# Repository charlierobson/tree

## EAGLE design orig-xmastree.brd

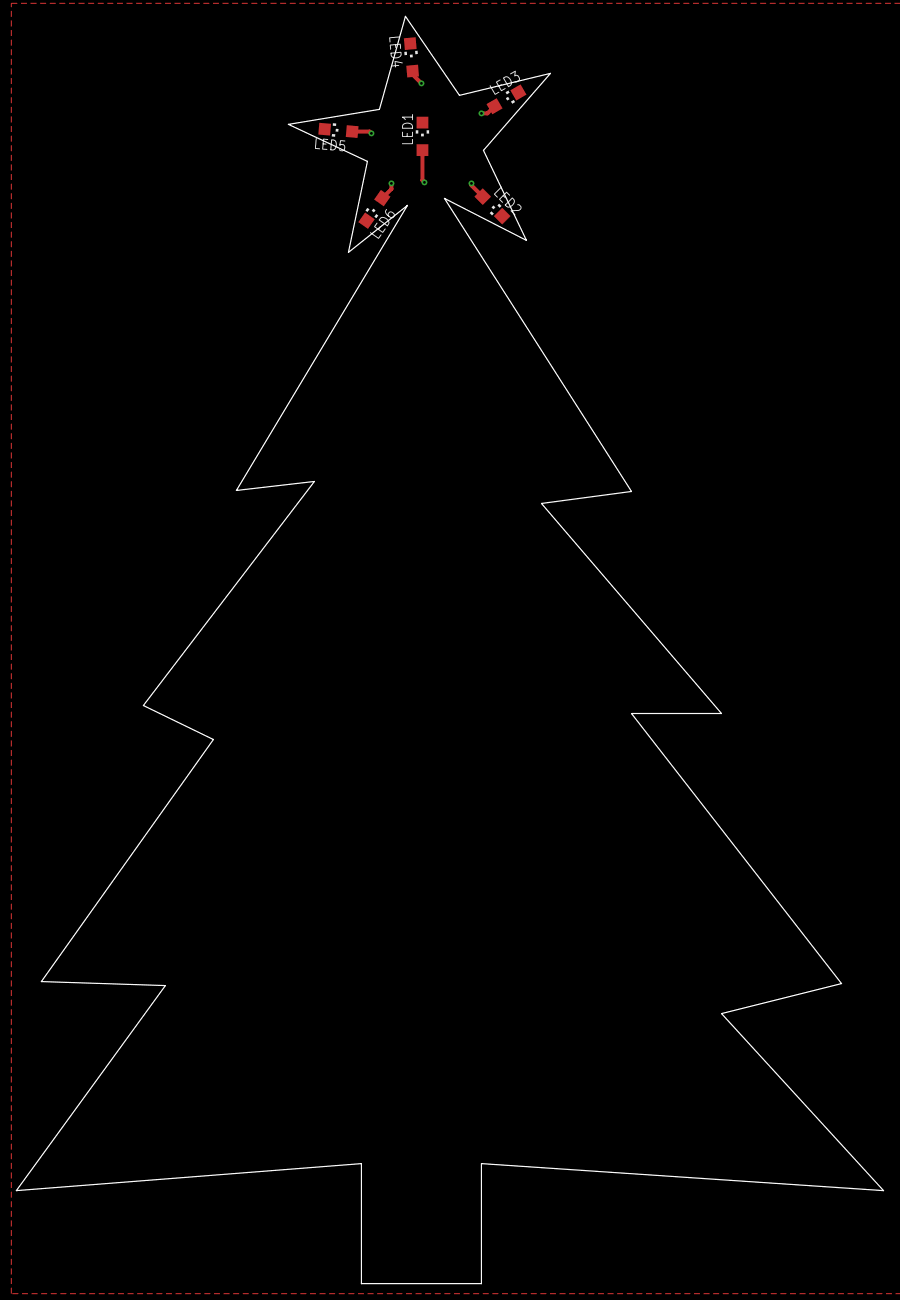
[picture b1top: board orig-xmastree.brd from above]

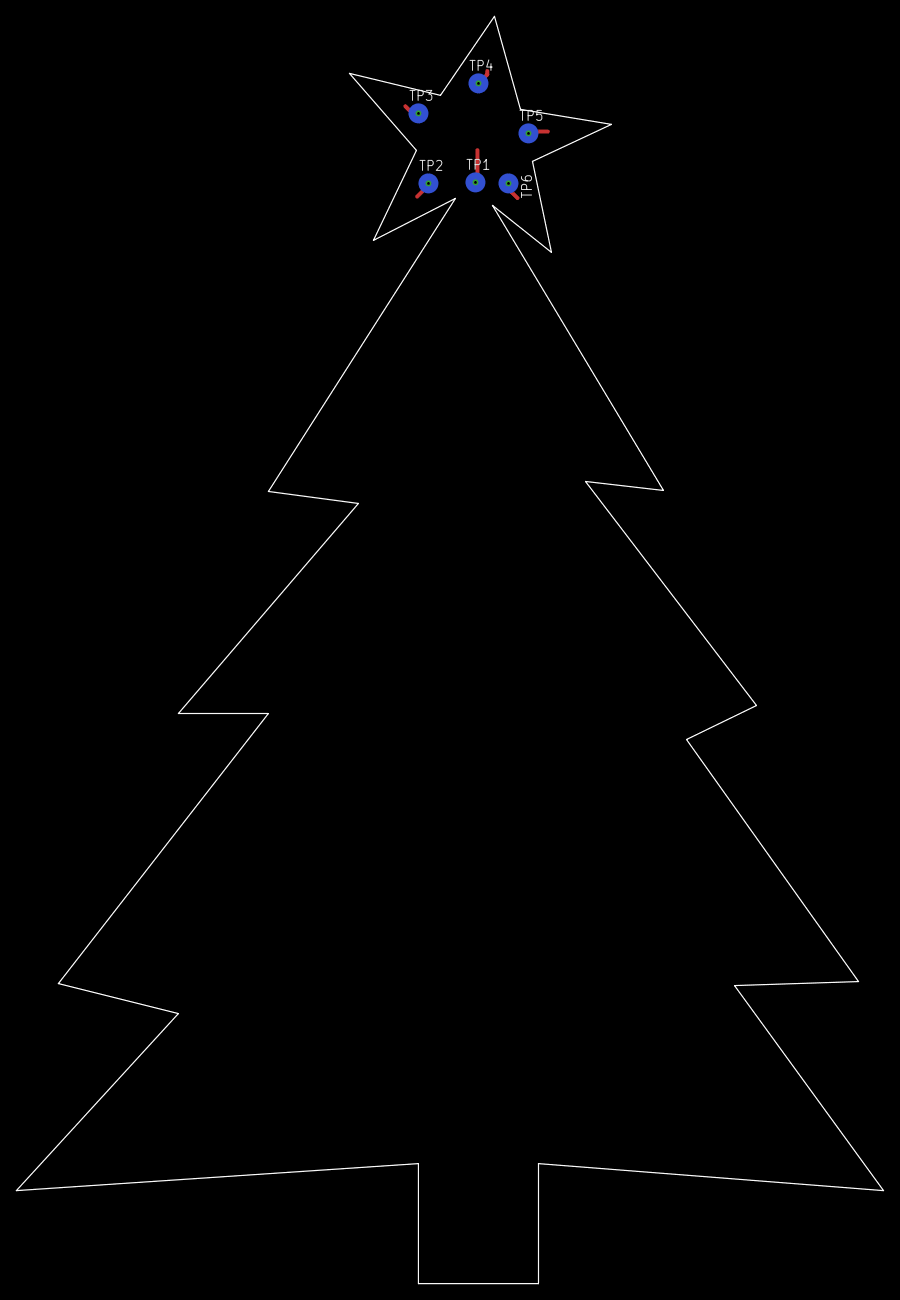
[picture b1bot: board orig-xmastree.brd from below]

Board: 2 copper layers, 110.1 x 160.9 mm, 12 parts (6 on the bottom side), 7 nets.

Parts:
LED1, LED2, LED3, LED4, LED5, LED6: CHIPLED_1206
TP1, TP2, TP3, TP4, TP5, TP6: TPB2,54; B2,54

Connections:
GND: LED1.C, LED2.C, LED3.C, LED4.C, LED5.C, LED6.C
unnamed: LED1.A, TP1.TP
unnamed: LED2.A, TP2.TP
unnamed: LED3.A, TP3.TP
unnamed: LED4.A, TP4.TP
unnamed: LED5.A, TP5.TP
unnamed: LED6.A, TP6.TP

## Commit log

2020-12-15 init push
